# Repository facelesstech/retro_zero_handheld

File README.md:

# retro_zero_handheld
retro_zero_handheld

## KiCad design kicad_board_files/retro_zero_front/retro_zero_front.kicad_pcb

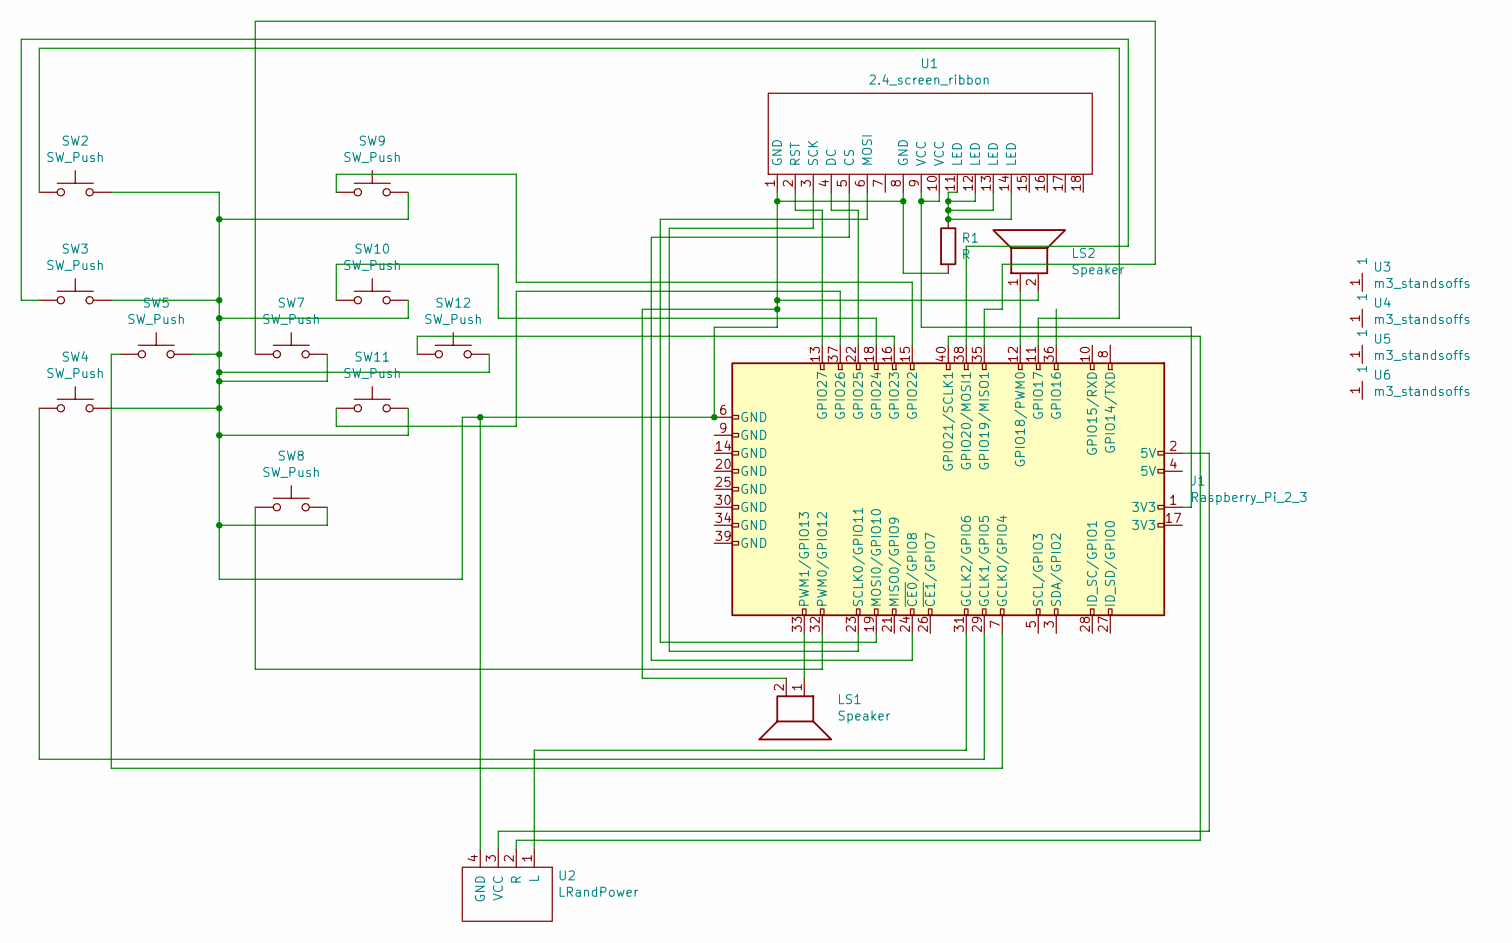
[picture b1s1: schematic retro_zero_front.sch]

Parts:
J1: Raspberry_Pi_2_3; raspberry_pi_gpio_smd_outline_custom
LS1, LS2: Speaker; piezo_smd
R1: R; R_1206_3216Metric
SW2, SW3, SW4, SW5, SW7, SW8, SW9, SW10, SW11, SW12: SW_Push; smd_soft_custom
U1: 2.4_screen_ribbon; 2.4_screen_ribbon_breakout
U2: LRandPower
U3, U4, U5, U6: m3_standsoffs; m3_hole_custom

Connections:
unnamed: J1.1 (3V3), U1.9 (VCC), U1.10 (VCC)
unnamed: J1.2 (5V), U2.3 (VCC)
unnamed: J1.6 (GND), LS1.2, LS2.2, R1.2, SW2.2, SW3.2, SW4.2, SW5.2, SW7.2, SW8.2, SW9.2, SW10.2, SW11.2, SW12.2, U1.1 (GND), U1.8 (GND), U2.4 (GND)
unnamed: J1.7 (GCLK0/GPIO4), SW5.1
unnamed: J1.11 (GPIO17), SW2.1
unnamed: J1.12 (GPIO18/PWM0), LS2.1
unnamed: J1.13 (GPIO27), U1.2 (RST)
unnamed: J1.15 (GPIO22), SW9.1
unnamed: J1.16 (GPIO23), SW12.1
unnamed: J1.18 (GPIO24), SW10.1
unnamed: J1.19 (MOSI0/GPIO10), U1.6 (MOSI)
unnamed: J1.22 (GPIO25), U1.4 (DC)
unnamed: J1.23 (SCLK0/GPIO11), U1.3 (SCK)
unnamed: J1.24 (~CE0~/GPIO8), U1.5 (CS)
unnamed: J1.29 (GCLK1/GPIO5), SW4.1
unnamed: J1.31 (GCLK2/GPIO6), U2.1 (L)
unnamed: J1.32 (PWM0/GPIO12), SW8.1
unnamed: J1.33 (PWM1/GPIO13), LS1.1
unnamed: J1.35 (GPIO19/MISO1), SW7.1
unnamed: J1.37 (GPIO26), SW11.1
unnamed: J1.38 (GPIO20/MOSI1), SW3.1
unnamed: J1.40 (GPIO21/SCLK1), U2.2 (R)
unnamed: R1.1, U1.11 (LED), U1.12 (LED), U1.13 (LED), U1.14 (LED)

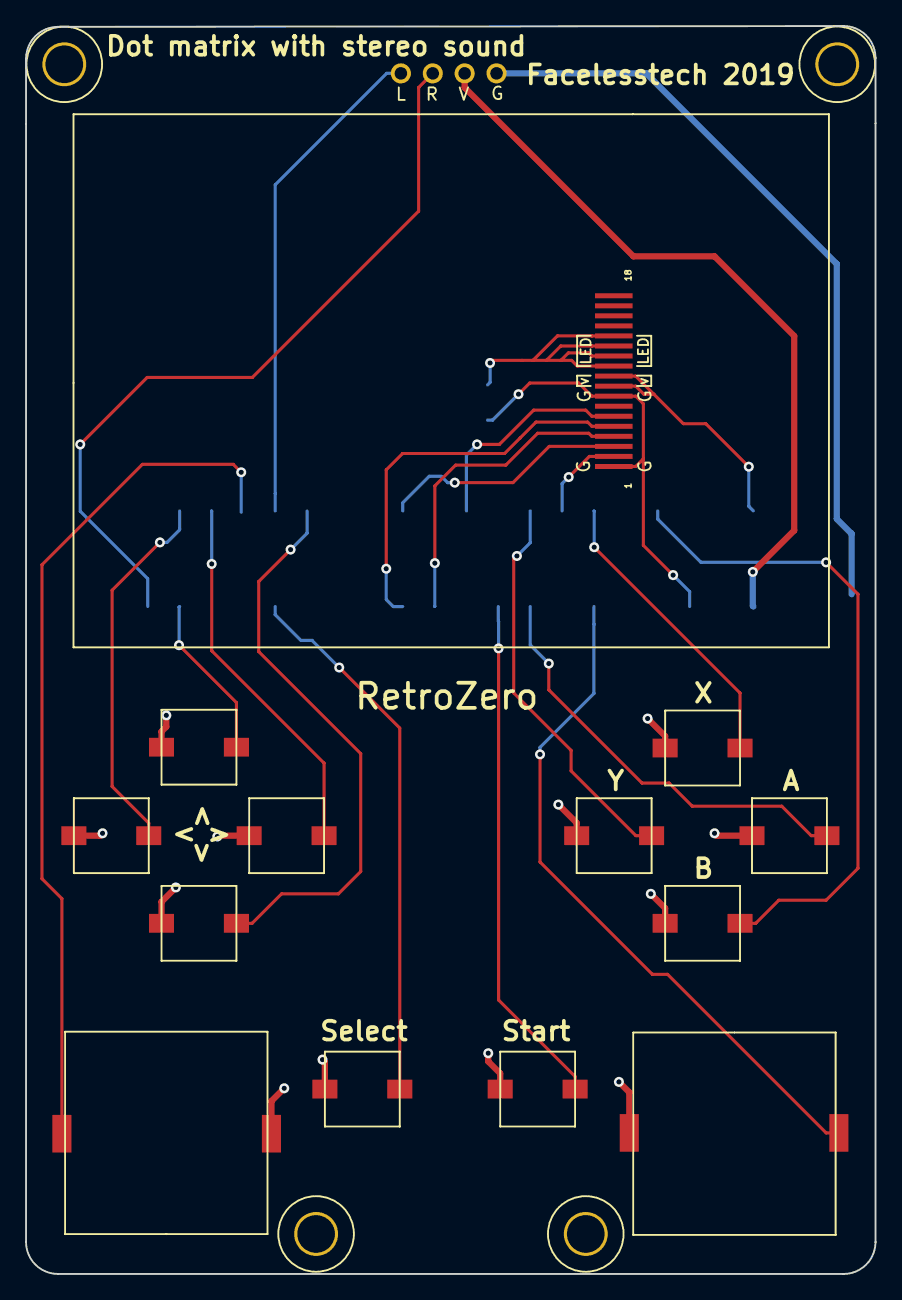
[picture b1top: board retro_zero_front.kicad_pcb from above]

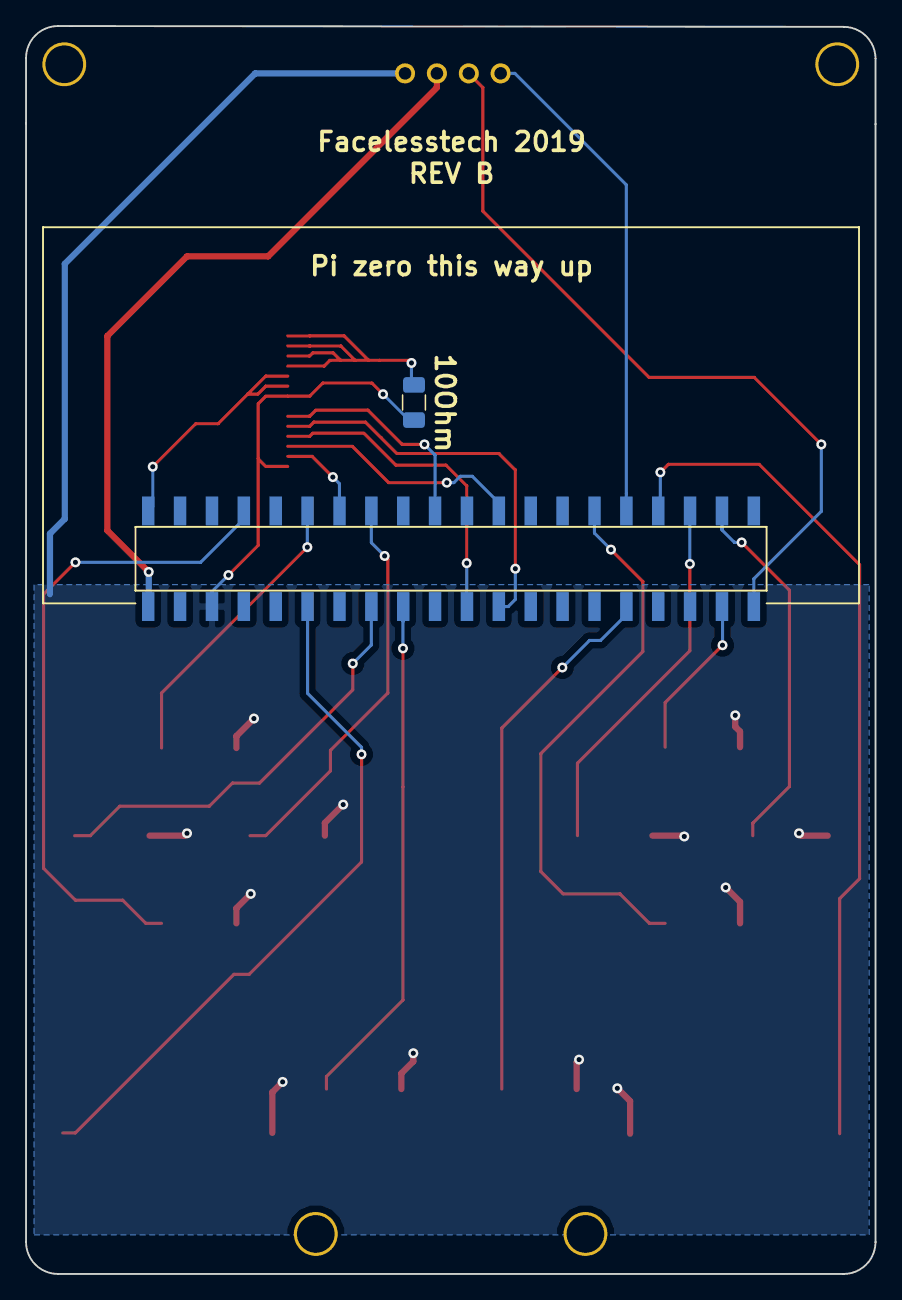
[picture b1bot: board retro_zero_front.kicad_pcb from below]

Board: 2 copper layers, 67.7 x 99.4 mm, 20 parts (2 on the bottom side), 23 nets.

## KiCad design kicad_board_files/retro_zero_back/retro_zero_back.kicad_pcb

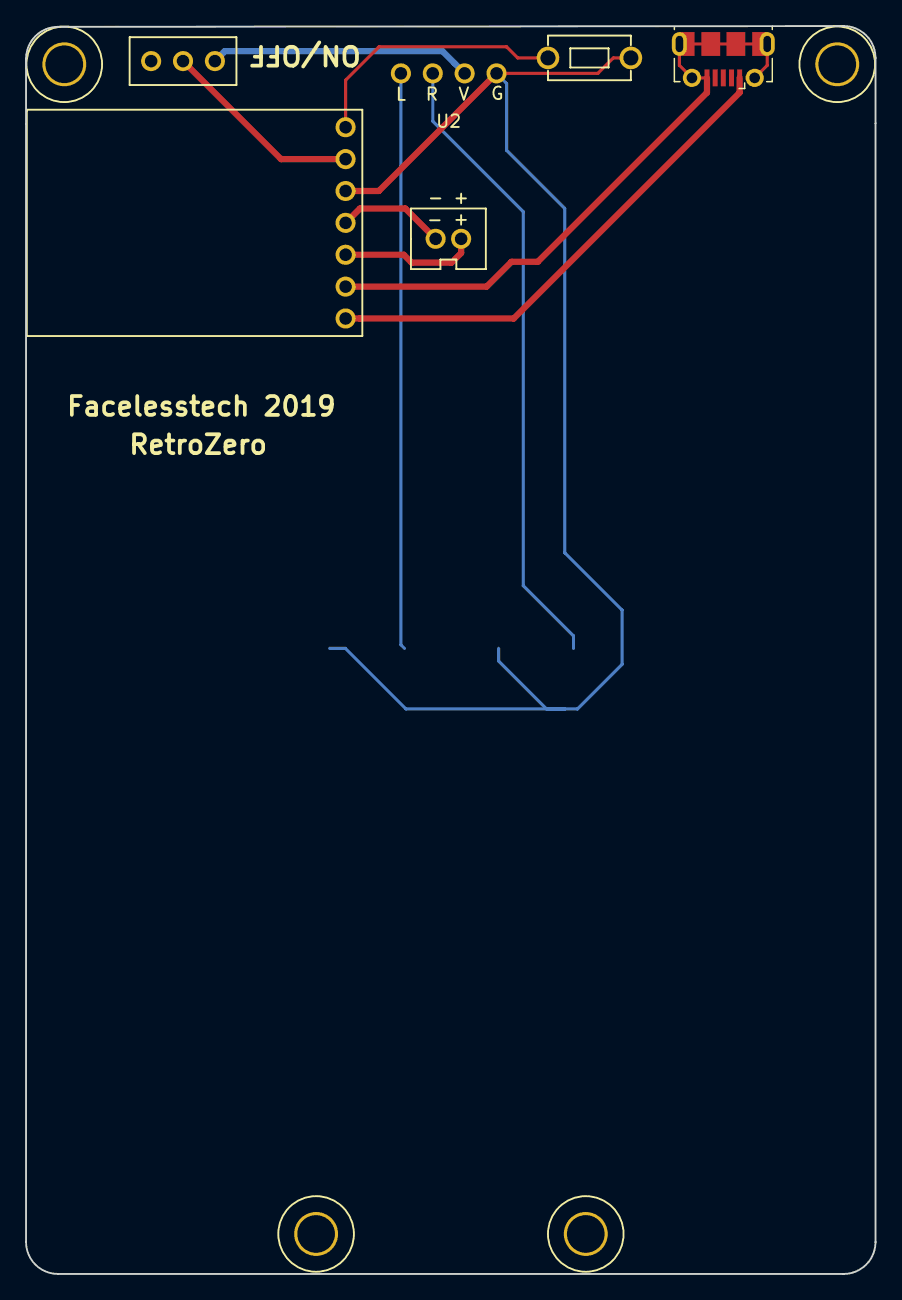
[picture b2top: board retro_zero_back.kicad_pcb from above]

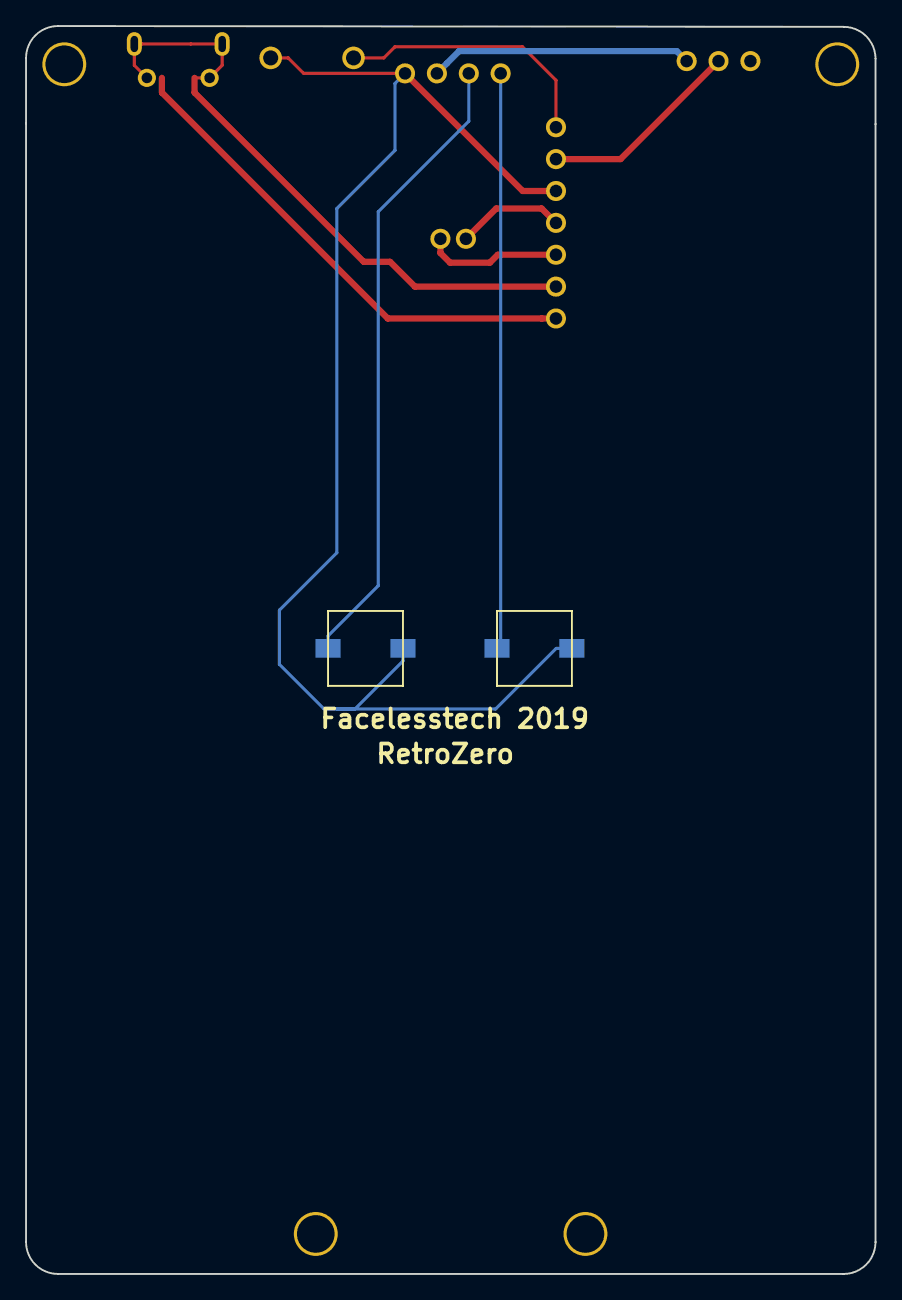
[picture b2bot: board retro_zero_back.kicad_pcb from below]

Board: 2 copper layers, 67.7 x 99.4 mm, 12 parts (2 on the bottom side), 10 nets.

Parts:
J1: USB_B_Micro; USB_Micro-B_Molex-105017-0001
SW1: SW_SPDT; 3_pin_switch_custom
SW2: SW_Push; small_button_2pin_custom
SW3, SW4: SW_Push; smd_soft_custom
U1: battery_custom; jst_2pin_custom
U2: LRandPower
U3, U4, U5, U6: m3_standsoffs; m3_hole_custom
U7: power_bank_green

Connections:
unnamed: J1.1, U7.1
unnamed: J1.5, J1.6, U7.2
unnamed: SW1.1, U2.3
unnamed: SW1.2, U7.6
unnamed: SW2.1, U7.7
unnamed: SW2.2, SW3.2, SW4.2, U2.4, U7.5
unnamed: SW3.1, U2.2
unnamed: SW4.1, U2.1
unnamed: U1.1, U7.4
unnamed: U1.2, U7.3

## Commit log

2019-04-06 board files
